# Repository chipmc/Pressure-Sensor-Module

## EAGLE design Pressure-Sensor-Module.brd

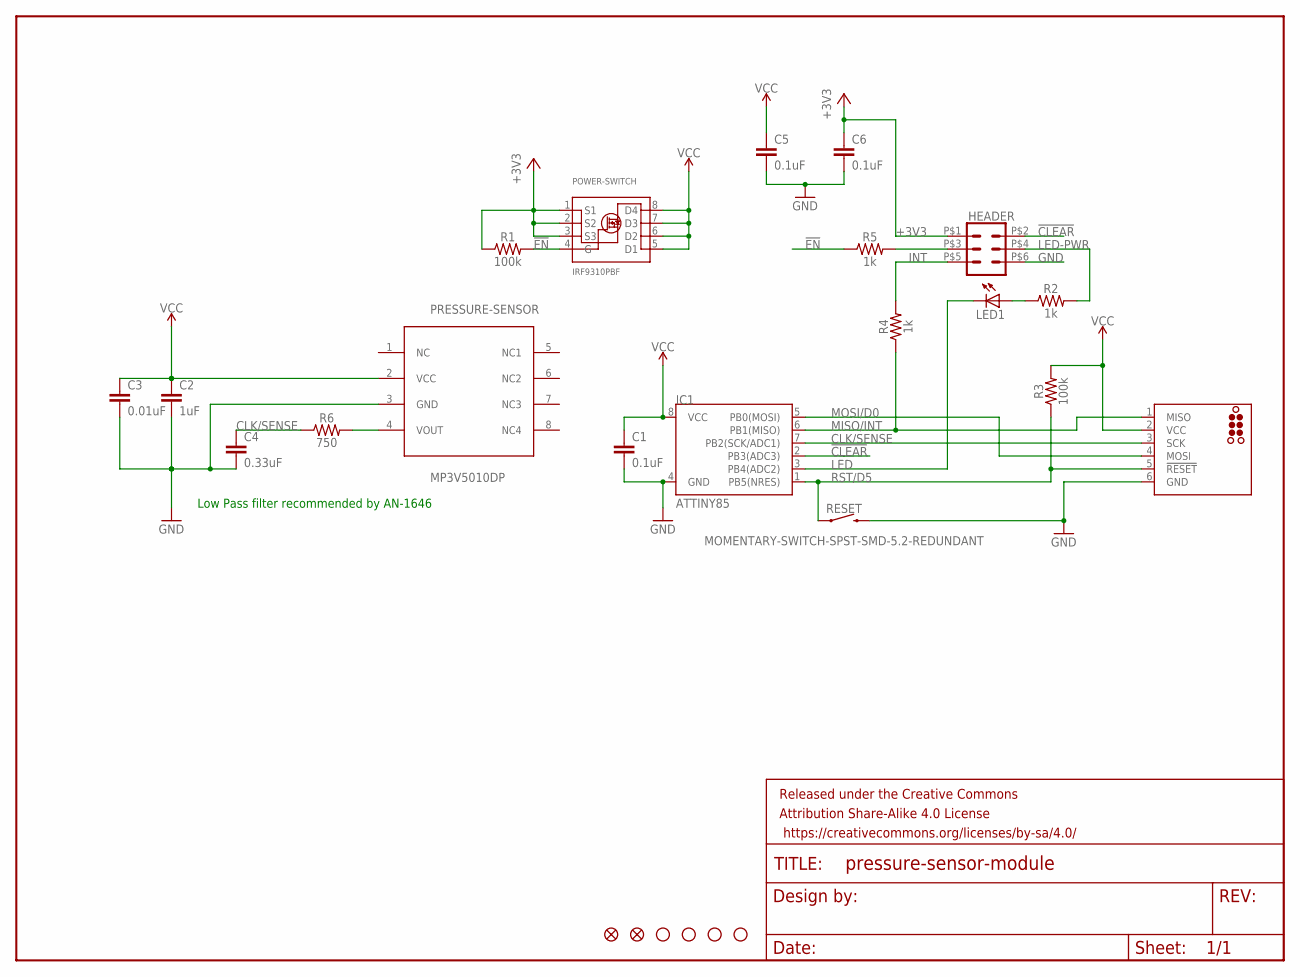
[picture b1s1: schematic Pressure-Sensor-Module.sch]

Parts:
C1, C5, C6: 0.1uF; 0805
C2: 1uF; 0805
C3: 0.01uF; 0805
C4: 0.33uF; 0805
FD1, FD2: FIDUCIALUFIDUCIAL; FIDUCIAL-MICRO
FRAME1: FRAME-LETTER; CREATIVE_COMMONS
HEADER: CONN_03X2POGO_PINS; 2X3_POGO
IC1: ATTINY85; SO08-EIAJ
ICSP: TC2030-MCP-NL
JP3, JP4, JP5, JP6: STAND-OFF
LED1: LEDCHIP-LED0805; CHIP-LED0805
POWER-SWITCH: IRF9310PBF; SO8-GW300
PRESSURE-SENSOR: MP3V5010DP; MP3V5010
R1, R3: 100k; 0805
R2, R4, R5: 1k; 0805
R6: 750; 0805
RESET: MOMENTARY-SWITCH-SPST-SMD-5.2-REDUNDANT; TACTILE_SWITCH_SMD_5.2MM

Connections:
!CLEAR!: HEADER.P$2 (2), IC1.2 (PB3(ADC3))
!EN!: POWER-SWITCH.4 (G), R1.2, R5.1
+3V3: C6.1, HEADER.P$1 (1), POWER-SWITCH.1 (S1), POWER-SWITCH.2 (S2), POWER-SWITCH.3 (S3), R1.1
CLK/SENSE: C4.1, IC1.7 (PB2(SCK/ADC1)), ICSP.3 (SCK), R6.1
GND: C1.2, C2.2, C3.2, C4.2, C5.2, C6.2, HEADER.P$6 (6), IC1.4 (GND), ICSP.6 (GND), PRESSURE-SENSOR.3 (GND), RESET.3 (2), RESET.4 (2)
INT: HEADER.P$5 (5), R4.2
LED: IC1.3 (PB4(ADC2)), LED1.C
LED-PWR: HEADER.P$4 (4), R2.2
MISO/INT: IC1.6 (PB1(MISO)), ICSP.1 (MISO), R4.1
MOSI/D0: IC1.5 (PB0(MOSI)), ICSP.4 (MOSI)
unnamed: LED1.A, R2.1
unnamed: HEADER.P$3 (3), R5.2
unnamed: PRESSURE-SENSOR.4 (VOUT), R6.2
NC: PRESSURE-SENSOR.1 (NC)
NC1: PRESSURE-SENSOR.5 (NC1)
RST/D5: IC1.1 (PB5(NRES)), ICSP.5 (!RESET), R3.1, RESET.1, RESET.2 (1)
VCC: C1.1, C2.1, C3.1, C5.1, IC1.8 (VCC), ICSP.2 (VCC), POWER-SWITCH.5 (D1), POWER-SWITCH.6 (D2), POWER-SWITCH.7 (D3), POWER-SWITCH.8 (D4), PRESSURE-SENSOR.2 (VCC), R3.2

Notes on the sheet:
Low Pass filter recommended by AN-1646

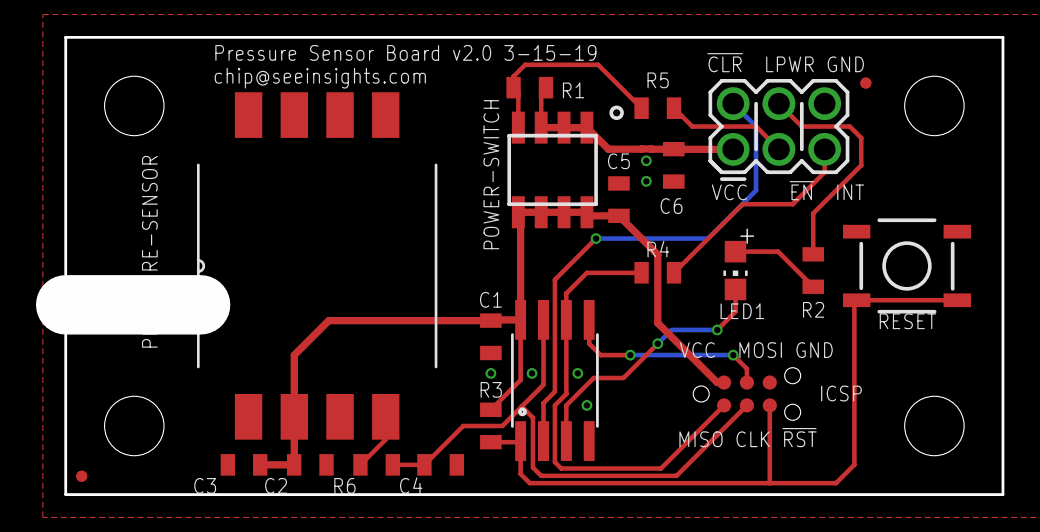
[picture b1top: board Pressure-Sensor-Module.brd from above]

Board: 2 copper layers, 52.1 x 25.4 mm, 26 parts (0 on the bottom side), 15 nets.

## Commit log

2019-03-15 v2 Pressure Sensor Board
2019-03-19 v2.0 Release Candidate

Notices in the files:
parts and their libraries:
SparkFun-Aesthetics: Licensing: Creative Commons ShareAlike 4.0 International - https://creativecommons.org/licenses/by-sa/4.0
SparkFun-Aesthetics: Released under the Creative Commons Attribution Share-Alike 4.0 License
SparkFun-Aesthetics: https://creativecommons.org/licenses/by-sa/4.0
